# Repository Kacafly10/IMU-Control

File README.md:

# Iiiriomote/Abracadibri

### /HID/Joystick/Game-stick/key-stick/\*

It was fun to use a wiimote with the wii, but it's nativs to only the wii. I want to play Beat Saber on PC, but it only supports VR. How to bridge all this? Make a similar HID ofc!

> Based on cutting edge RF Tech with native gesture binding support, bringing a seamless Experience to IMU based HIDs.

If I were a company witha big r&d team that might be it. but no, I'm a **chief hardware junior** so it's times worse.

### Features

- 2 + 1D output
- solid IMU tracking with less than .5mm error at any given time
- Adjustable sensitivity or at least a nice level of sensiticity.
- ergo form factor
- USB C + **_Wireless_** connectivity (BLE6)
- Z-axis gestures

### Choice of MCU

nRF54l15 - FPU + Low latency Wirelesses.

### PCB

`Schematic`

`Layout`

### 3D Design

`Main`

`Lid`

[Onshape](https://cad.onshape.com/documents/98a41b9541d161cd48b5abd8/w/a6aa8765be7e5cd60379758f/e/afb3d6cf83ac2bb12e1dc333)

### BOM

| Name                  | Qty | Unit  | Price  | Total  | Link                                                  |
| --------------------- | --- | ----- | ------ | ------ | ----------------------------------------------------- |
| 2000mAh LiPo with NTC | 1   | pcs   | 5.35   | 5.35   | https://www.aliexpress.com/item/1005008638516854.html |
| WeAct Mini Debugger   | 1   | pcs   | 3.48   | 3.48   | https://www.aliexpress.com/item/1005005303809188.html |
| or                    |     |       |        |        |                                                       |
| J-link Clone          | 1   | pcs   | 19.21  | 19.21  | https://www.aliexpress.com/item/1005008248107434.html |
| PCB(3/2A)             | 1   | order | 112.34 | 112.34 |                                                       |
| Case Printing         | 1   | pcs   |        |        |                                                       |
| Total                 |     |       |        | 139.38 | TBF                                                   |

[BOM](bom.csv)

### Code

nRF Connect SDK Using C/C++. I'm not confident in my Cxxxx skills so IDK. I chose this because it is native for nRF MCU.

Using standard zephyr sensor & RTIO libs + a custom(?) nRF HoG Profile.

repo: [fw](https://github.com/Kacafly10/fw_iiiriomote-abracadibri)

### Differece to or from a Wiimote

uhh

Connects seamlessly to any BLE HoG(basically Bluetooth for peripheral) compatible device.
Open
Modern

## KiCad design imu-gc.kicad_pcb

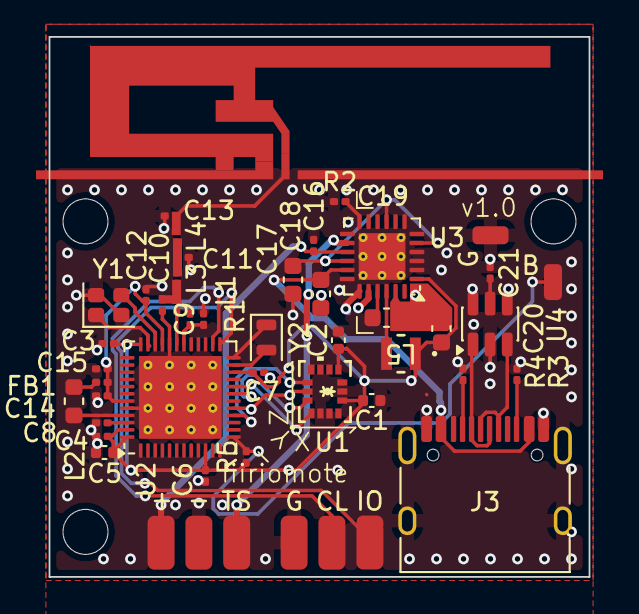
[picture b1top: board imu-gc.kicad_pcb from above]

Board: 4 copper layers, 30.0 x 30.0 mm, 48 parts (0 on the bottom side), 35 nets.

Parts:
+: Pin1; SolderWirePad_1x01_SMD_1.5x3mm
-: Pin2; SolderWirePad_1x01_SMD_1.5x3mm
B: Pin; SolderWirePad_1x01_SMD_1x2mm
C1, C2: 100nF; C_0402_1005Metric
C3, C4, C6, C7, C21: 100nF; C_0201_0603Metric
C5: 10uF; C_0402_1005Metric
C8, C12, C15: 2.2uF; C_0201_0603Metric
C9: 3.9pF; C_0201_0603Metric
C10: 1.5pF; C_0201_0603Metric
C11: 2pF; C_0201_0603Metric
C13: 0.3pF; C_0201_0603Metric
C14: 10nF; C_0201_0603Metric
C16: 1uF; C_0201_0603Metric
C17: 2.2uF; C_0603_1608Metric
C18, C19, C20: 10uF; C_0603_1608Metric
CL: Pin; SolderWirePad_1x01_SMD_1.5x3mm
FB1: L_0201_0603Metric
G: Pin; SolderWirePad_1x01_SMD_1x2mm
G#2: Pin; SolderWirePad_1x01_SMD_1.5x3mm
IO: Pin; SolderWirePad_1x01_SMD_1.5x3mm
J3: USB_C_Receptacle_USB2.0_14P; USB_C_Receptacle_HRO_TYPE-C-31-M-12
J8: Conn_01x02_Pin; Inverted_F_Antenna_2.4Ghz_1.0mmPCB_TI_CC2430DB.pretty
L1: 2.7nH; L_0201_0603Metric
L2: 4.7uH; L_0603_1608Metric
L3, L4: 3.5nH; L_0201_0603Metric
L5: 2.2uH; APH201610C2R2MP01
R1: 1k; R_0201_0603Metric
R2: 1.5k; R_0201_0603Metric
R3, R4: 5.1k; R_0201_0603Metric
R5: 4.7k; R_0201_0603Metric
TS: Pin3; SolderWirePad_1x01_SMD_1.5x3mm
U1: LSM6DS3TR-C; QFN_S3TR-C_STM
U2: nRF54L15-QFXX; QFN-48-1EP_6x6mm_P0.4mm_EP4.6x4.6mm_ThermalVias
U3: nPM1100-QDXX; QFN-24-1EP_4x4mm_P0.5mm_EP2.6x2.6mm_ThermalVias
U4: USBLC6-2SC6; SOT-23-6
Y1: 32Mhz; Crystal_SMD_2016-4Pin_2.0x1.6mm
Y2: 32.768khz; Crystal_SMD_2012-2Pin_2.0x1.2mm

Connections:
/3v3: C1.1, C2.1, C3.1, C4.1, C5.1, C6.1, C7.1, C20.1, L5.1, R5.1, U1.5 (VDDIO), U1.8 (VDD), U2.10 (VDD), U2.22 (VDD), U2.36 (VDD), U2.47 (VDD), U2.48 (VDD), U3.1 (VOUTB)
/IMU_CLK: U1.13 (SCL), U2.17 (P2.06)
/IMU_CS: U1.12 (CS), U2.16 (P2.05)
/IMU_MISO: U1.1 (SDO/SA0), U2.20 (P2.09)
/IMU_MOSI: U1.14 (SDA), U2.19 (P2.08)
/NTC: TS.1 (Pin_1_1), U3.14 (NTC)
/RF: C13.1, J8.1, L4.2
/SWDCLK: CL.1 (Pin_1_1), U2.26 (SWDCLK)
/SWDIO: IO.1 (Pin_1_1), U2.25 (SWDIO)
/SYS_D+: U3.20 (D+), U4.4 (I/O2)
/SYS_D-: U3.19 (D-), U4.6 (I/O1)
/USB_5V: C17.1, J3.A4 (VBUS), J3.A9 (VBUS), J3.B4 (VBUS), J3.B9 (VBUS), U3.17 (VBUS)
/USB_D+: J3.A6 (D+), J3.B6 (D+), U4.3 (I/O2)
/USB_D-: J3.A7 (D-), J3.B7 (D-), U4.1 (I/O1)
/VSYS: C18.1, U3.5 (ISET), U3.9 (VTERMSET), U3.16 (VSYS)
GND: -.1 (Pin_1_1), C1.2, C2.2, C3.2, C4.2, C5.2, C6.2, C7.2, C8.2, C9.2, C10.2, C11.2, C12.2, C13.2, C14.2, C15.2, C16.2, C17.2, C18.2, C19.2, C20.2, C21.1, G.1 (Pin_1_1), G#2.1 (Pin_1_1), J3.A1 (GND), J3.A12 (GND), J3.B1 (GND), J3.B12 (GND), J3.SH (SHIELD), J8.2, R2.2, R3.2, R4.2, U1.2 (SDx), U1.3 (SCx), U1.6 (GND), U1.7 (GND), U2.32 (VSS_PA), U2.44 (VSS), U2.49 (VSS), U3.2 (VOUTBSET1), U3.3 (VOUTBSET0), U3.4 (AVSS), U3.23 (PVSS), U3.25 (AVSS), U4.2 (GND), Y1.2 (G), Y1.4 (G)
unnamed: C10.1, L1.2, L3.1
unnamed: C11.1, L3.2, L4.1
unnamed: +.1 (Pin_1_1), C16.1, U3.15 (VBAT)
unnamed: J3.A5 (CC1), R4.1
unnamed: J3.B5 (CC2), R3.1
unnamed: B.1 (Pin_1_1), R5.2, U2.13 (P2.02)
unnamed: L1.1, U2.31 (ANT)
unnamed: C8.1, FB1.2, L2.2, U2.46 (DCC)
unnamed: C12.1, C14.1, C15.1, FB1.1, U2.33 (DECRF), U2.43 (DECA)
unnamed: L2.1, U2.45 (DECD)
unnamed: U2.23 (P0.00), Y2.2
unnamed: U2.24 (P0.01), Y2.1
unnamed: U2.34 (XC1), Y1.3
unnamed: U2.35 (XC2), Y1.1
unnamed: C9.1, R1.1, U2.30 (~RESET)
unnamed: C19.1, U3.21 (DEC)
unnamed: R2.1, U3.12 (ICHG)
unnamed: L5.2, U3.22 (SW)
unnamed: C21.2, U4.5 (VBUS)

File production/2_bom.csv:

Designator,Footprint,Quantity,Value,LCSC Part #
+,SolderWirePad_1x01_SMD_1.5x3mm,1,Pin1,
-,SolderWirePad_1x01_SMD_1.5x3mm,1,Pin2,
"C1, C2",0402,2,100nF,
C10,0201,1,1.5pF,
C11,0201,1,2pF,
"C12, C15, C8",0201,3,2.2uF,
C13,0201,1,0.3pF,
C14,0201,1,10nF,
C16,0201,1,1uF,
C17,0603,1,2.2uF,
"C18, C19, C20",0603,3,10uF,
"C21, C3, C4, C6, C7",0201,5,100nF,
C5,0402,1,10uF,
C9,0402,1,3.9pF,
"CL, G, IO",SolderWirePad_1x01_SMD_1.5x3mm,3,Pin,
FB1,0201,1,~,
J3,USB_C_Receptacle_HRO_TYPE-C-31-M-12,1,USB_C_Receptacle_USB2.0_14P,
J8,Inverted_F_Antenna_2.4Ghz_1.0mmPCB_TI_CC2430DB.pretty,1,Conn_01x02_Pin,
L1,0201,1,2.7nH,
L2,0603,1,4.7uH,
"L3, L4",0201,2,3.5nH,
L5,APH201610C2R2MP01,1,2.2uH,
R1,0201,1,1k,
R2,0201,1,1.5k,
"R3, R4",0201,2,5.1k,
TS,SolderWirePad_1x01_SMD_1.5x3mm,1,Pin3,
U1,QFN_S3TR-C_STM,1,LSM6DS3TR-C,
U2,QFN-48-1EP_6x6mm_P0.4mm_EP4.6x4.6mm_ThermalVias,1,nRF54L15-QFXX,
U3,QFN-24-1EP_4x4mm_P0.5mm_EP2.6x2.6mm_ThermalVias,1,nPM1100-QDXX,
U4,SOT-23-6,1,USBLC6-2SC6,
Y1,Crystal_SMD_2016-4Pin_2.0x1.6mm,1,32Mhz,
Y2,Crystal_SMD_2012-2Pin_2.0x1.2mm,1,32.768khz,
